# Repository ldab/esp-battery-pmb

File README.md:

# ESP-battery-pmb

ESP32, ESP8266 and the likes Battery Management Board, Power your device with a single Battery or 2xAAA. With a buit-in Boost and Buck converter + Nano Timer - Sleep Current < 1uA.

## TODO

- [ ] More details about battery etc...

## Efficiency

## Schematic

## Enclosure

## BOM

[ESP Battery pmb](./KiCad/BOM.csv)

## Final Thoughts or Improvements

* 

## Credits

GitHub Shields and Badges created with [Shields.io](https://github.com/badges/shields/)

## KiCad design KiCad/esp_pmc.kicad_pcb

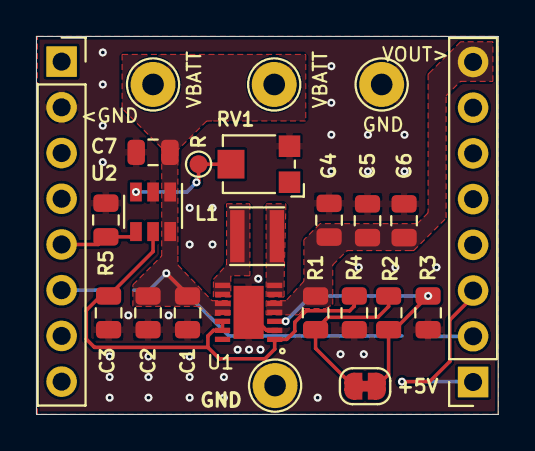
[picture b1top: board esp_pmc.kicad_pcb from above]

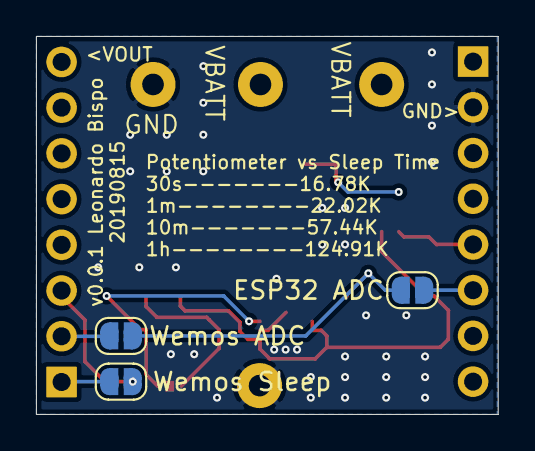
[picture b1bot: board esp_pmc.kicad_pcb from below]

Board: 2 copper layers, 25.7 x 21.0 mm, 27 parts (3 on the bottom side), 14 nets.

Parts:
C1, C2, C4, C5, C6: 10u; C_0805_2012Metric
C3, C7: 100n; C_0805_2012Metric
J1, J2: Conn_01x08_Female; PinSocket_1x08_P2.54mm_Vertical
JP1: ESP32 ADC; SolderJumper-2_P1.3mm_Open_RoundedPad1.0x1.5mm
JP2: Wemos Sleep; SolderJumper-2_P1.3mm_Open_RoundedPad1.0x1.5mm
JP3: Wemos ADC; SolderJumper-2_P1.3mm_Open_RoundedPad1.0x1.5mm
JP4: SolderJumper_2_Bridged; SolderJumper-2_P1.3mm_Bridged_RoundedPad1.0x1.5mm
L1: 1u; L_Taiyo-Yuden_NR-30xx
R1: 1M±0.1%; R_0805_2012Metric
R2: 604K±1%; R_0805_2012Metric
R3: 180k±1%; R_0805_2012Metric
R4, R5: 10K; R_0805_2012Metric
RV1: 200K; Potentiometer_Bourns_TC33X_Vertical
TP1, TP2, TP3, TP3#2: TestPoint; TestPoint_THTPad_D2.5mm_Drill1.2mm
TP4: TestPoint; TestPoint_Pad_D1.0mm
U1: TPS63020DSJR; SON50P300X400X100-15N-D
U2: TPL5111; SOT-23-6

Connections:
/M_DRV: RV1.2, TP4.1, U2.3
/Sleep: J2.1, JP2.1
ADC: C1.1, C2.1, C7.1, JP1.2, JP3.1, TP1.1, TP2.1, U1.10, U1.11, U2.1, U2.6
DONE: J1.5, R5.1, U2.4
EN: C3.1, R4.1, U1.1, U1.12, U1.13, U2.5
GND: C1.2, C2.2, C3.2, C4.2, C5.2, C6.2, C7.2, J1.2, R3.2, R4.2, R5.2, RV1.3, TP3.1, TP3#2.1, U1.2, U1.15, U2.2
unnamed: J1.6, JP1.1
unnamed: J2.2, JP3.2
unnamed: J2.3, JP2.2
unnamed: JP4.1, R1.2, R2.1
unnamed: JP4.2, R2.2, R3.1, U1.3
unnamed: L1.1, U1.6, U1.7
unnamed: L1.2, U1.8, U1.9
VOUT: C4.1, C5.1, C6.1, J2.8, R1.1, U1.4, U1.5

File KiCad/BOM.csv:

Id,Designator,Package,Quantity,Designation,Supplier and ref,Column1,_1
1,"TP3,TP3,TP2,TP1",TestPoint_THTPad_D2.5mm_Drill1.2mm,4,TestPoint,,,
2,TP4,TestPoint_Pad_D1.0mm,1,TestPoint,,,
3,"J1,J2",PinSocket_1x08_P2.54mm_Vertical,2,Conn_01x08_Female,,,
4,U2,SOT-23-6,1,TPL5111,,,
5,U1,SON50P300X400X100-15N-D,1,TPS63020DSJR,,,
6,RV1,Potentiometer_Bourns_TC33X_Vertical,1,200K,,,
7,"R5,R4",R_0805_2012Metric,2,10K,,,
8,R3,R_0805_2012Metric,1,180k±1%,,,
9,R2,R_0805_2012Metric,1,604K±1%,,,
10,R1,R_0805_2012Metric,1,1M±0.1%,,,
11,L1,L_Taiyo-Yuden_NR-30xx,1,1u,,,
12,JP4,SolderJumper-2_P1.3mm_Bridged_RoundedPad1.0x1.5mm,1,SolderJumper_2_Bridged,,,
13,JP1,SolderJumper-2_P1.3mm_Open_RoundedPad1.0x1.5mm,1,ESP32 ADC,,,
14,JP2,SolderJumper-2_P1.3mm_Open_RoundedPad1.0x1.5mm,1,Wemos Sleep,,,
15,JP3,SolderJumper-2_P1.3mm_Open_RoundedPad1.0x1.5mm,1,Wemos ADC,,,
16,"C7,C3",C_0805_2012Metric,2,100n,,,
17,"C6,C5,C4,C2,C1",C_0805_2012Metric,5,10u,,,

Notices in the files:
README.md:
License: MIT
